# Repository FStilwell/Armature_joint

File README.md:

# Armature_joint
This repository serves as a location for relevant work regarding the Armature Joint module as my Level 7 Engineering Development Project at WelTec.

## Overview

In-depth details on the project can be found in the "project_report.pdf" file in the "documentation" folder.

### Mechanical Structure

The solidworks 3D files for the joint modules can be found in the "Mechanical_structure" folder. The solidworks files are quite messy with unorganised links in the model. Therefore, I would recommend that the concepts would be used rather than building directly from the solidworks files.

The details behind my thinking with the mechanical structure can be  found in the project report under the "5. Project Design/methodology" section.

### Electronics

All the electronics files and information are found under the "PCB" folder. More in-depth details on the electronics are found in the project report under the "5. Project Design/methodology" section.

#### Rework and test info

A document with the test info for each of the boards is found under the PCB/Board_testing directory. There are a few LEDs that were placed incorrectly and there's a design error with the reset button.

### Software

More details on the software can be found in the project report under the "5. Project Design/methodology" section.

The software that I worked on is found under SDKs/nRF5_SDK_14.2.0_17b948a/examples/my_examples. They are Segger Embedded Studio project files. There are two programs that I think might be useful which are the blinky projects below.

A blink program is found under SDKs/nRF5_SDK_14.2.0_17b948a/examples/my_examples/Armature_joint_blinky_4-working/

A BLE blink program is found under SDKs/nRF5_SDK_14.2.0_17b948a/examples/my_examples/ble_app_blinky-working/

#### Configuring projects to work with the Armature boards

A guide I wrote for configuring the Segger Embedded Studio example projects to work with the armature boards can be found at Documentation/Modifying_SDK_SES_examples_for_Armature.pdf

#### Programming the boards

Using the Segger J-Link Edu Mini and a custom ribbon cable with a 6 pin header, I was programming the boards using the native Segger Embedded Studio toolchain. The header is connected to to the board as shown in the image below.

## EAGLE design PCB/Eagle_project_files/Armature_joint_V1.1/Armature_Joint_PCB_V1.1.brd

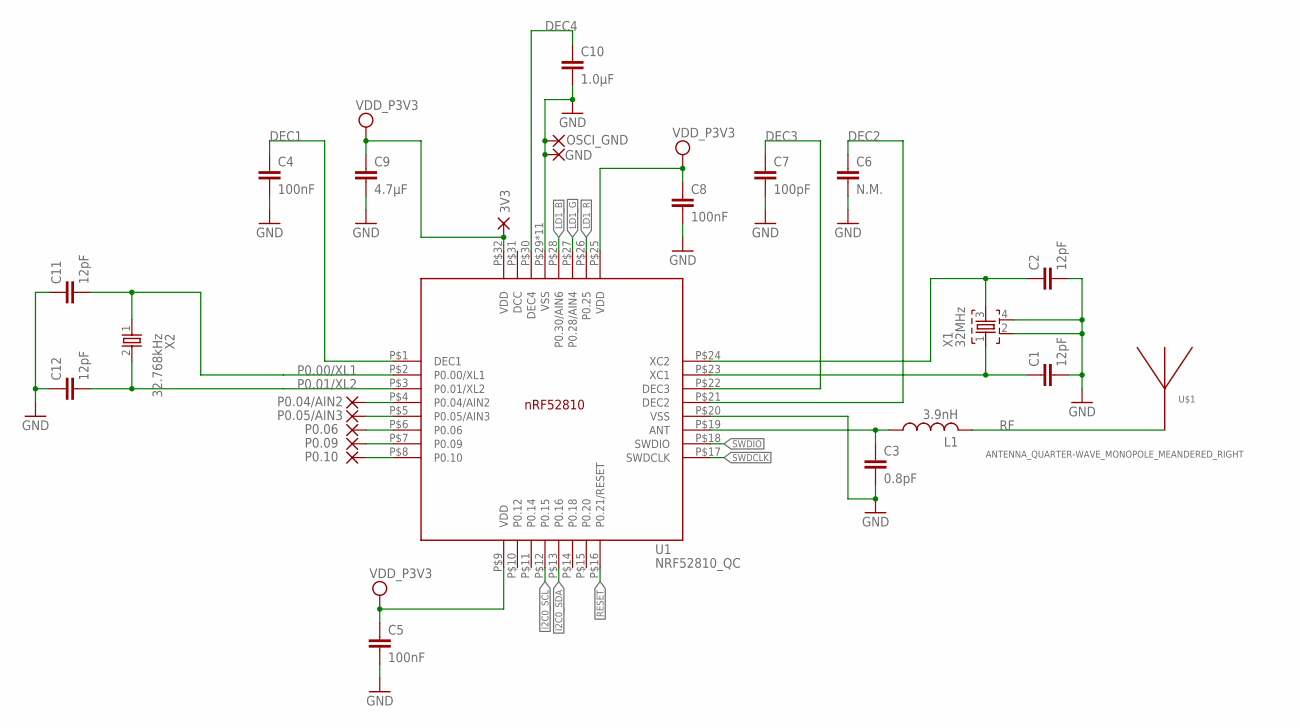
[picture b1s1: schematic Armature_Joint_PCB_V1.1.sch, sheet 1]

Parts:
3V3: vdd_p3v3; SMD1,27-2,54
C1, C2, C11, C12: 12pF; RESC0402_N
C3: 0.8pF; RESC0402_N
C4, C5, C8: 100nF; RESC0402_N
C6: N.M.; RESC0402_N
C7: 100pF; RESC0402_N
C9: 4.7µF; RESC0603_N
C10: 1.0µF; RESC0603_N
GND: GND; SMD1,27-2,54
L1: 3.9nH; RESC0402_N
OSCI_GND: GND; 2,15/1,0
P0.04/AIN2: P0.04/AIN2; SMD1,27-2,54
P0.05/AIN3: P0.05/AIN3; SMD1,27-2,54
P0.06: P0.06; SMD1,27-2,54
P0.09: P0.09; SMD1,27-2,54
P0.10: P0.10; SMD1,27-2,54
U1: NRF52810_QC; QFN50P500X500X90-32_N
U$1: ANTENNA_QUARTER-WAVE_MONOPOLE_MEANDERED_RIGHT; QWMP_MEANDERED_RIGHT_+6
X1: 32MHz; BT-XTAL_2016_N
X2: 32.768kHz; XTAL_3215_N

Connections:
ANT: C3.1, L1.1, U1.P$19 (ANT)
DEC1: C4.1, U1.P$1 (DEC1)
DEC2: C6.1, U1.P$21 (DEC2)
DEC3: C7.1, U1.P$22 (DEC3)
DEC4: C10.1, U1.P$30 (DEC4)
GND: C1.2, C2.2, C3.2, C4.2, C5.2, C6.2, C7.2, C8.2, C9.2, C10.2, C11.1, C12.1, GND.1, OSCI_GND.1, U1.P$20 (VSS), U1.P$29 (VSS), U1.P$33 (VSS), U1.P$34 (VSS), U1.P$35 (VSS), U1.P$36 (VSS), U1.P$37 (VSS), U1.P$38 (VSS), U1.P$39 (VSS), U1.P$40 (VSS), U1.P$41 (VSS), U1.P$42 (VSS), X1.2, X1.4; also elsewhere on the board
I2C0_SCL: U1.P$12 (P0.15); also elsewhere on the board
I2C0_SDA: U1.P$13 (P0.16); also elsewhere on the board
LD1_B: U1.P$28 (P0.30/AIN6); also elsewhere on the board
LD1_G: U1.P$27 (P0.28/AIN4); also elsewhere on the board
LD1_R: U1.P$26 (P0.25); also elsewhere on the board
unnamed: C2.1, U1.P$24 (XC2), X1.3
P0.00/XL1: C11.2, U1.P$2 (P0.00/XL1), X2.1
P0.01/XL2: C12.2, U1.P$3 (P0.01/XL2), X2.2
P0.04/AIN2: P0.04/AIN2.1, U1.P$4 (P0.04/AIN2)
P0.05/AIN3: P0.05/AIN3.1, U1.P$5 (P0.05/AIN3)
P0.06: P0.06.1, U1.P$6 (P0.06)
P0.09: P0.09.1, U1.P$7 (P0.09)
P0.10: P0.10.1, U1.P$8 (P0.10)
RESET: U1.P$16 (P0.21/RESET); also elsewhere on the board
RF: L1.2, U$1.P$1
SWDCLK: U1.P$17 (SWDCLK); also elsewhere on the board
SWDIO: U1.P$18 (SWDIO); also elsewhere on the board
VDD_P3V3: 3V3.1, C5.1, C8.1, C9.1, U1.P$9 (VDD), U1.P$25 (VDD), U1.P$32 (VDD); also elsewhere on the board
X1: C1.1, U1.P$23 (XC1), X1.1

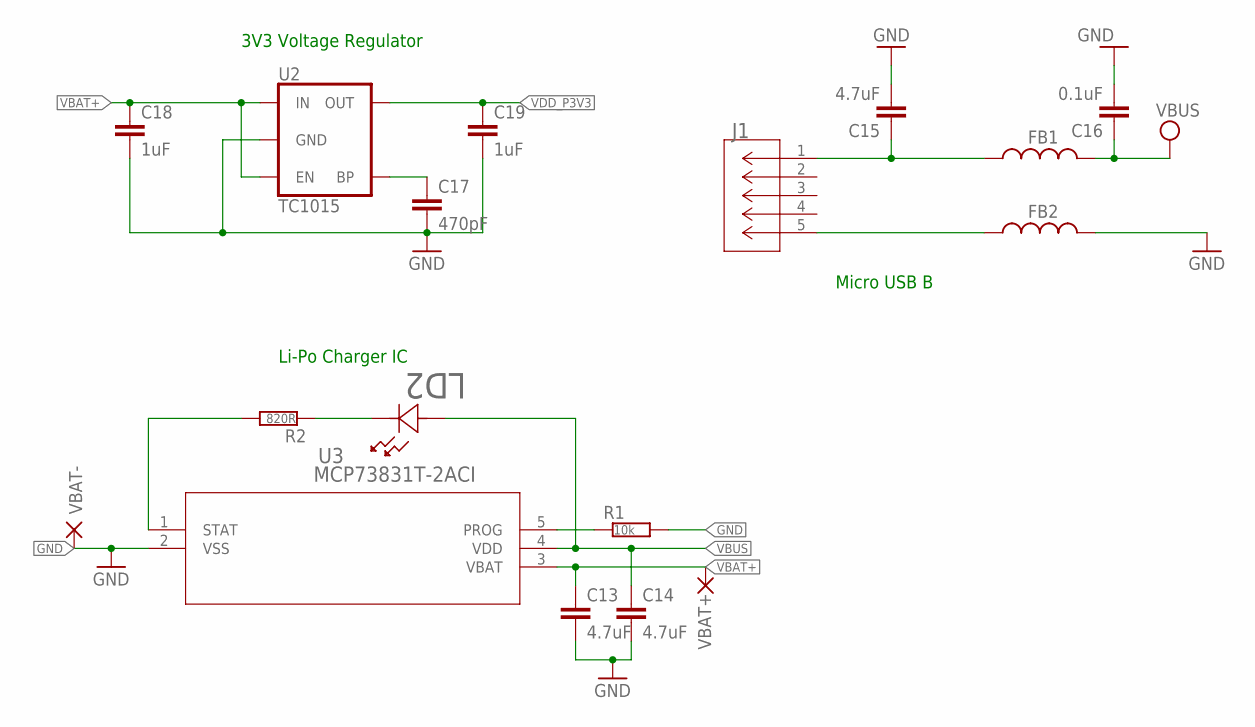
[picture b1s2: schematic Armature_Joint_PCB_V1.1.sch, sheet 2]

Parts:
C13, C14, C15: 4.7uF; RESC0603_N
C16: 0.1uF; RESC0603_N
C17: 470pF; RESC0402_N
C18, C19: 1uF; RESC0603_N
FB1, FB2: FERRITE_BEAD; RESC0402_M
J1: 10118192-0002LF; CONN_10118192-0002LF_AMP
LD2: LBQH9G-N1OO-35-1; LED_SML-LX0402SYC-TR_LUM-M
R1: 10k; RESC0402_N
R2: 820R; RESC0402_N
U2: TC1015; SOT23-5
U3: MCP73831T-2ACI; SOT-23-5_MC_MCH
VBAT+: VBAT+; SMD1,27-2,54
VBAT-: GND; SMD1,27-2,54

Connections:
GND: C13.2, C14.2, C15.2, C16.2, C17.2, C18.2, C19.2, FB2.2, R1.2, U2.2 (GND), U3.2 (VSS), VBAT-.1; also elsewhere on the board
unnamed: LD2.1, R2.1
unnamed: C17.1, U2.4 (BP)
unnamed: R1.1, U3.5 (PROG)
unnamed: R2.2, U3.1 (STAT)
unnamed: C15.1, FB1.1, J1.1
unnamed: FB2.1, J1.5
VBAT+: C13.1, C18.1, U2.1 (IN), U2.3 (EN), U3.3 (VBAT), VBAT+.1
VBUS: C14.1, C16.1, FB1.2, LD2.2, U3.4 (VDD)
VDD_P3V3: C19.1, U2.5 (OUT); also elsewhere on the board

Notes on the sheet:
3V3 Voltage Regulator
Li-Po Charger IC
Micro USB B

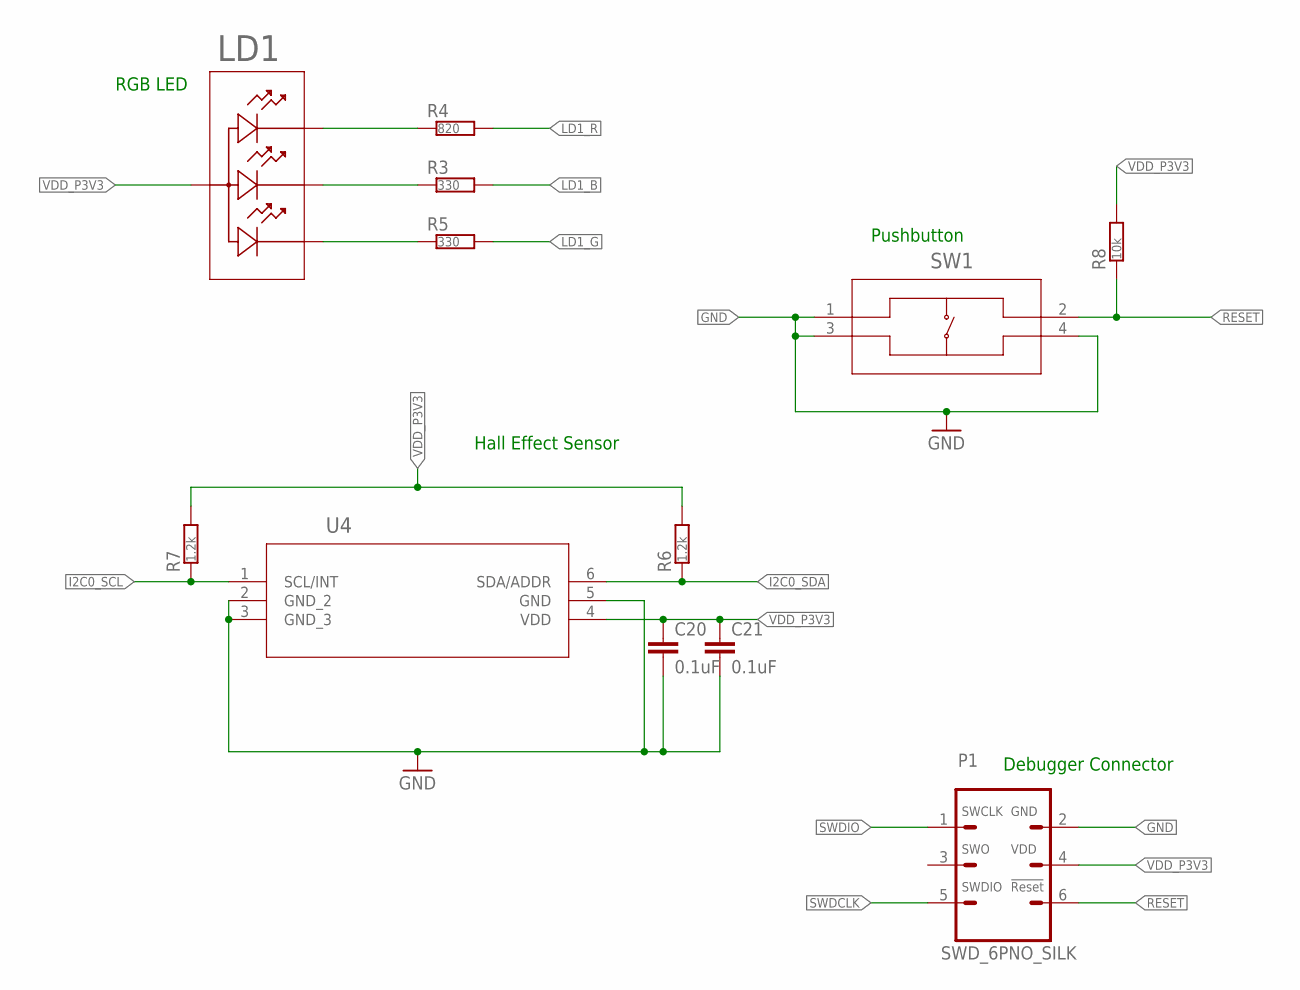
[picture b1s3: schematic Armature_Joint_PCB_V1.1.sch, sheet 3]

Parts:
C20, C21: 0.1uF; RESC0402_M
LD1: APHF1608SEEQBDZGKCAPHF1608SEEQBDZGKC_KNB-L; APHF1608SEEQBDZGKC_KNB-L
P1: SWD_6PNO_SILK; SWD_6P
R3, R5: 330; RESC0402_N
R4: 820; RESC0402_N
R6, R7: 1.2k; RESC0402_N
R8: 10k; RESC0402_N
SW1: PTS810SJG250SMTRLFS; PTS810
U4: TLV493DA1B6HTSA2; PG-TSOP6-6-5_INF

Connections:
GND: C20.2, C21.2, P1.2, SW1.1, SW1.3, SW1.4, U4.2 (GND_2), U4.3 (GND_3), U4.5 (GND); also elsewhere on the board
I2C0_SCL: R7.1, U4.1 (SCL/INT); also elsewhere on the board
I2C0_SDA: R6.1, U4.6 (SDA/ADDR); also elsewhere on the board
LD1_B: R3.2; also elsewhere on the board
LD1_G: R5.2; also elsewhere on the board
LD1_R: R4.2; also elsewhere on the board
unnamed: LD1.4, R5.1
unnamed: LD1.3, R3.1
unnamed: LD1.2, R4.1
RESET: P1.6, R8.1, SW1.2; also elsewhere on the board
SWDCLK: P1.5; also elsewhere on the board
SWDIO: P1.1; also elsewhere on the board
VDD_P3V3: C20.1, C21.1, LD1.1, P1.4, R6.2, R7.2, R8.2, U4.4 (VDD); also elsewhere on the board

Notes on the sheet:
Pushbutton
RGB LED
Hall Effect Sensor
Debugger Connector

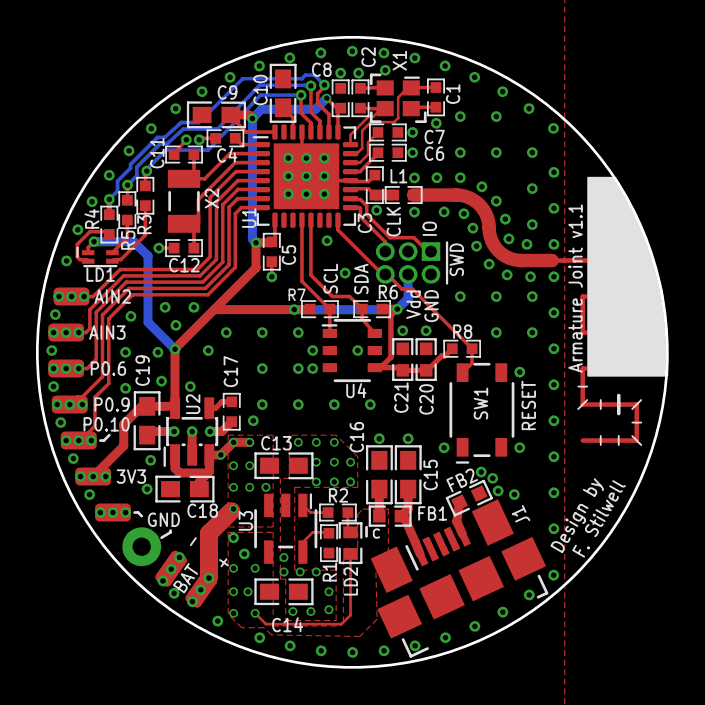
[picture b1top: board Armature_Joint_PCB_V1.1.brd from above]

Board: 2 copper layers, 35.0 x 35.0 mm, 54 parts (0 on the bottom side), 36 nets.

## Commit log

2020-11-18 added v14.2 SDK
2020-11-18 added PDF
2020-11-18 ignore Word files
2022-02-27 added sysnopsis and poster
2022-02-27 added project report
2022-02-27 added PDF of eagle schematic
2022-02-27 added an overview of the project files and info
2022-02-27 extra info referenced about software

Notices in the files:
parts and their libraries:
COPYRIGHT: Copyright (C) 2018 Accelerated Designs. All rights reserved
